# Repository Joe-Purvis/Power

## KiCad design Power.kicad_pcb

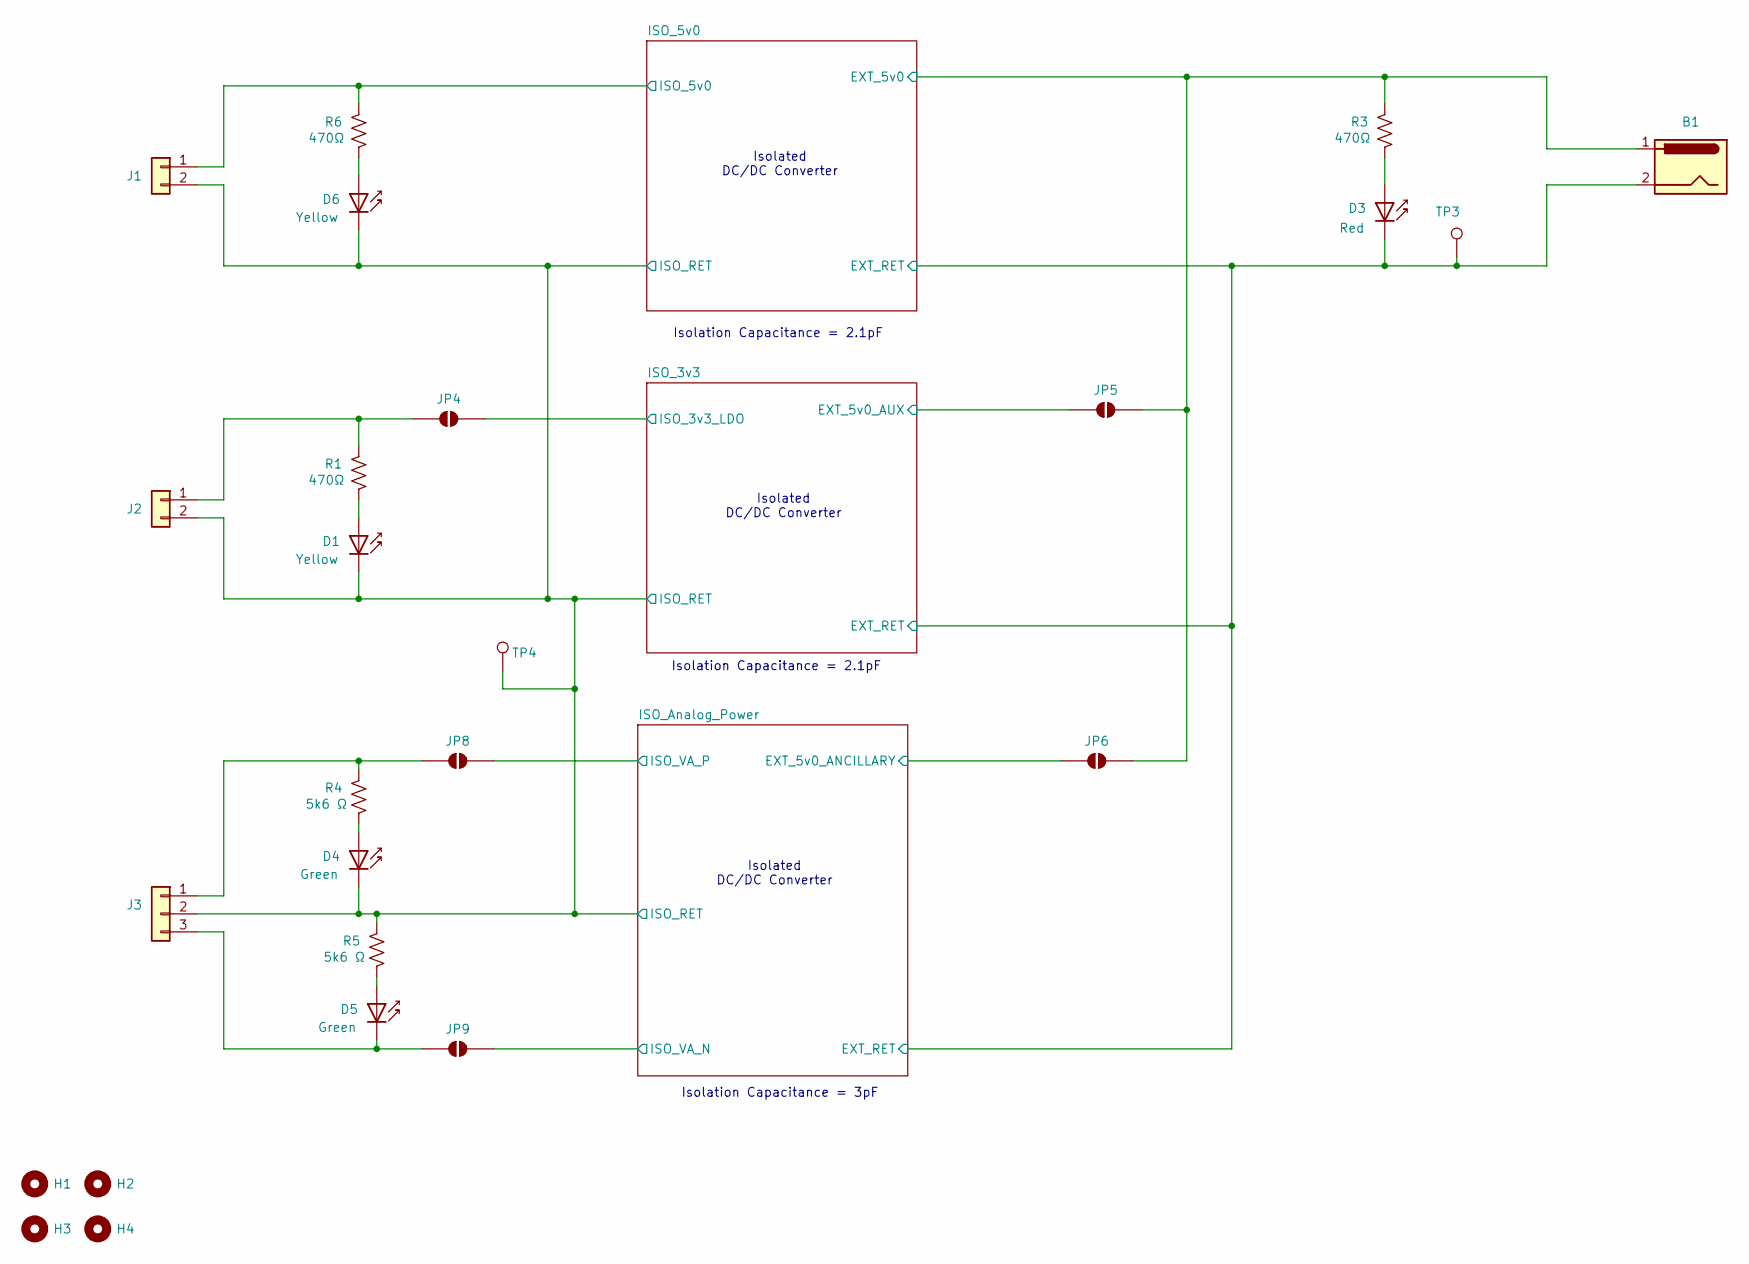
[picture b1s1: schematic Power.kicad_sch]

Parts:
B1: Barrel_Jack; BarrelJack_CUI_PJ-063AH_Horizontal
D1, D6: Yellow; LED_1206_3216Metric; LCSC C2298
D3: Red; LED_1206_3216Metric; LCSC C49018
D4, D5: Green; LED_1206_3216Metric; LCSC C14641
H1, H2, H3, H4: MountingHole; MountingHole_2.2mm_M2
J1, J2: Conn_01x02; PinHeader_1x02_P2.54mm_Vertical
J3: Conn_01x03; PinHeader_1x03_P2.54mm_Vertical
JP4, JP5, JP6, JP8, JP9: SolderJumper_2_Open; SolderJumper-2_P1.3mm_Open_RoundedPad1.0x1.5mm
R1, R3, R6: 470Ω; R_1206_3216Metric_Pad1.30x1.75mm_HandSolder; LCSC C4502
R4, R5: 5k6 Ω; R_1206_3216Metric_Pad1.30x1.75mm_HandSolder; Tolerance 5%; LCSC C2889795
TP3, TP4: TestPoint; TestPoint_Keystone_5000-5004_Miniature

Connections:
/ISO_3v3/EXT_5v0_AUX: JP5.1 (A); also elsewhere on the board
/ISO_3v3/EXT_RET: B1.2, D3.1 (K), TP3.1 (1_1); also elsewhere on the board
/ISO_3v3/ISO_3v3_LDO: JP4.2 (B); also elsewhere on the board
/ISO_5v0/EXT_5v0: B1.1, JP5.2 (B), JP6.2 (B), R3.2; also elsewhere on the board
/ISO_5v0/ISO_5v0: J1.1, R6.2; also elsewhere on the board
/ISO_Analog_Power/EXT_5v0_ANCILLARY: JP6.1 (A); also elsewhere on the board
/ISO_Analog_Power/ISO_RET: D1.1 (K), D4.1 (K), D6.1 (K), J1.2, J2.2, J3.2, R5.2, TP4.1 (1_1); also elsewhere on the board
/ISO_Analog_Power/ISO_VA_N: JP9.2 (B); also elsewhere on the board
/ISO_Analog_Power/ISO_VA_P: JP8.2 (B); also elsewhere on the board
unnamed: D1.2 (A), R1.1
unnamed: D3.2 (A), R3.1
unnamed: D4.2 (A), R4.1
unnamed: D5.2 (A), R5.1
unnamed: D5.1 (K), J3.3, JP9.1 (A)
unnamed: D6.2 (A), R6.1
unnamed: J2.1, JP4.1 (A), R1.2
unnamed: J3.1, JP8.1 (A), R4.2

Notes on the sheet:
Isolated DC/DC Converter
Isolation Capacitance = 2.1pF
Isolation Capacitance = 3pF

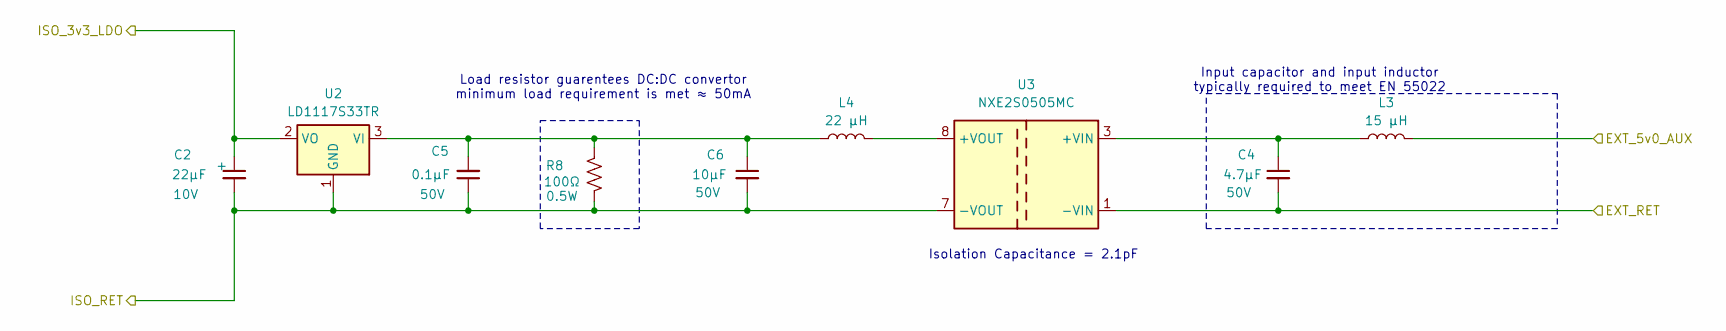
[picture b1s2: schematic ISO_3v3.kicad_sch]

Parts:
C2: 22µF; CP_EIA-3216-18_Kemet-A; Voltage Rating 10V; Tolerance 10%; LCSC C503893
C4: 4.7µF; C_1206_3216Metric; Voltage Rating 50V; LCSC C29823
C5: 0.1µF; C_1206_3216Metric_Pad1.33x1.80mm_HandSolder; Voltage Rating 50V; LCSC C24497
C6: 10µF; C_1206_3216Metric_Pad1.33x1.80mm_HandSolder; Voltage Rating 50V; LCSC C13585
L3: 15 µH; L_Changjiang_FNR4018S; Current Rating 1A; LCSC C167809
L4: 22 µH; L_Sunlord_SWPA5040; Current Rating 1.5A; LCSC C68434
R8: 100Ω; R_1206_3216Metric_Pad1.30x1.75mm_HandSolder; Voltage Rating 7.07V power-limited at 0.5W; series lim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; Tolerance 1%; LCSC C2978216
U2: LD1117S33TR; SOT-223-3_TabPin2; LCSC C86781
U3: NXE2S0505MC; Converter_DCDC_Murata_NXExSxxxxMC_SMD; LCSC C5817088

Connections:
/ISO_3v3/EXT_5v0_AUX: L3.2; also elsewhere on the board
/ISO_3v3/EXT_RET: C4.2, U3.1 (-VIN); also elsewhere on the board
/ISO_3v3/ISO_3v3_LDO: C2.1, U2.2 (VO); also elsewhere on the board
/ISO_Analog_Power/ISO_RET: C2.2, C5.1, C6.2, R8.1, U2.1 (GND), U3.7 (-VOUT); also elsewhere on the board
unnamed: C5.2, C6.1, L4.1, R8.2, U2.3 (VI)
unnamed: C4.1, L3.1, U3.3 (+VIN)
unnamed: L4.2, U3.8 (+VOUT)

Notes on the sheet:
Load resistor guarentees DC:DC convertor minimum load requirement is met ≈ 50mA
Input capacitor and input inductor typically required to meet EN 55022
Isolation Capacitance = 2.1pF

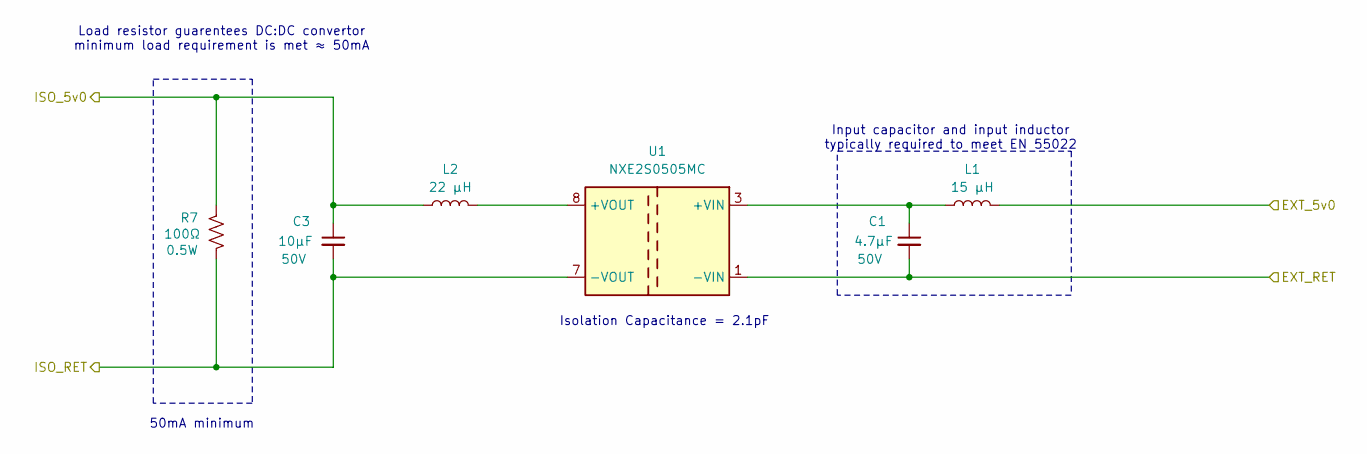
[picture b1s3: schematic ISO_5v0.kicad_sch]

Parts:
C1: 4.7µF; C_1206_3216Metric; Voltage Rating 50V; LCSC C29823
C3: 10µF; C_1206_3216Metric_Pad1.33x1.80mm_HandSolder; Voltage Rating 50V; LCSC C13585
L1: 15 µH; L_Changjiang_FNR4018S; Current Rating 1A; LCSC C167809
L2: 22 µH; L_Sunlord_SWPA5040; Current Rating 1.5A; LCSC C68434
R7: 100Ω; R_1206_3216Metric_Pad1.30x1.75mm_HandSolder; Voltage Rating 7.07V power-limited at 0.5W; series lim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; Tolerance 1%; LCSC C2978216
U1: NXE2S0505MC; Converter_DCDC_Murata_NXExSxxxxMC_SMD; LCSC C5817088

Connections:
/ISO_3v3/EXT_RET: C1.2, U1.1 (-VIN); also elsewhere on the board
/ISO_5v0/EXT_5v0: L1.2; also elsewhere on the board
/ISO_5v0/ISO_5v0: C3.1, L2.1, R7.2; also elsewhere on the board
/ISO_Analog_Power/ISO_RET: C3.2, R7.1, U1.7 (-VOUT); also elsewhere on the board
unnamed: C1.1, L1.1, U1.3 (+VIN)
unnamed: L2.2, U1.8 (+VOUT)

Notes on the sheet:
Load resistor guarentees DC:DC convertor minimum load requirement is met ≈ 50mA
Isolation Capacitance = 2.1pF
Input capacitor and input inductor typically required to meet EN 55022
50mA minimum

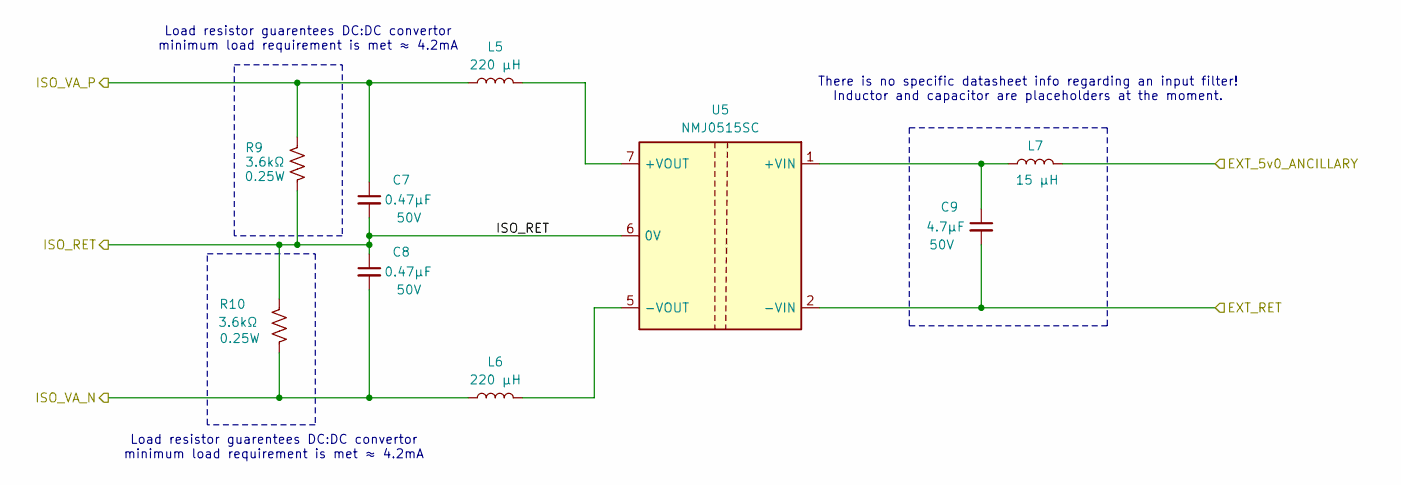
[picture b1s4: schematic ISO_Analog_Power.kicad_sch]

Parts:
C7, C8: 0.47µF; C_1206_3216Metric_Pad1.33x1.80mm_HandSolder; Voltage Rating 50V; LCSC C277483
C9: 4.7µF; C_1206_3216Metric; Voltage Rating 50V; LCSC C29823
L5, L6: 220 µH; L_Sunlord_SWPA4030; Current Rating 0.35A; LCSC C62495
L7: 15 µH; L_Changjiang_FNR4018S; Current Rating 1A; LCSC C167809
R9, R10: 3.6kΩ; R_1206_3216Metric_Pad1.30x1.75mm_HandSolder; Voltage Rating 30V power-limited at 0.25W; series limi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; Tolerance 1%; LCSC C137291
U5: NMJ0515SC

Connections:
/ISO_3v3/EXT_RET: C9.2, U5.2 (-VIN); also elsewhere on the board
/ISO_Analog_Power/EXT_5v0_ANCILLARY: L7.2; also elsewhere on the board
/ISO_Analog_Power/ISO_RET: C7.2, C8.1, R9.1, R10.2, U5.6 (0V); also elsewhere on the board
/ISO_Analog_Power/ISO_VA_N: C8.2, L6.1, R10.1; also elsewhere on the board
/ISO_Analog_Power/ISO_VA_P: C7.1, L5.1, R9.2; also elsewhere on the board
unnamed: C9.1, L7.1, U5.1 (+VIN)
unnamed: L5.2, U5.7 (+VOUT)
unnamed: L6.2, U5.5 (-VOUT)

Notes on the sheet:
Load resistor guarentees DC:DC convertor minimum load requirement is met ≈ 4.2mA
There is no specific datasheet info regarding an input filter! Inductor and capacitor are placeholders at the moment.

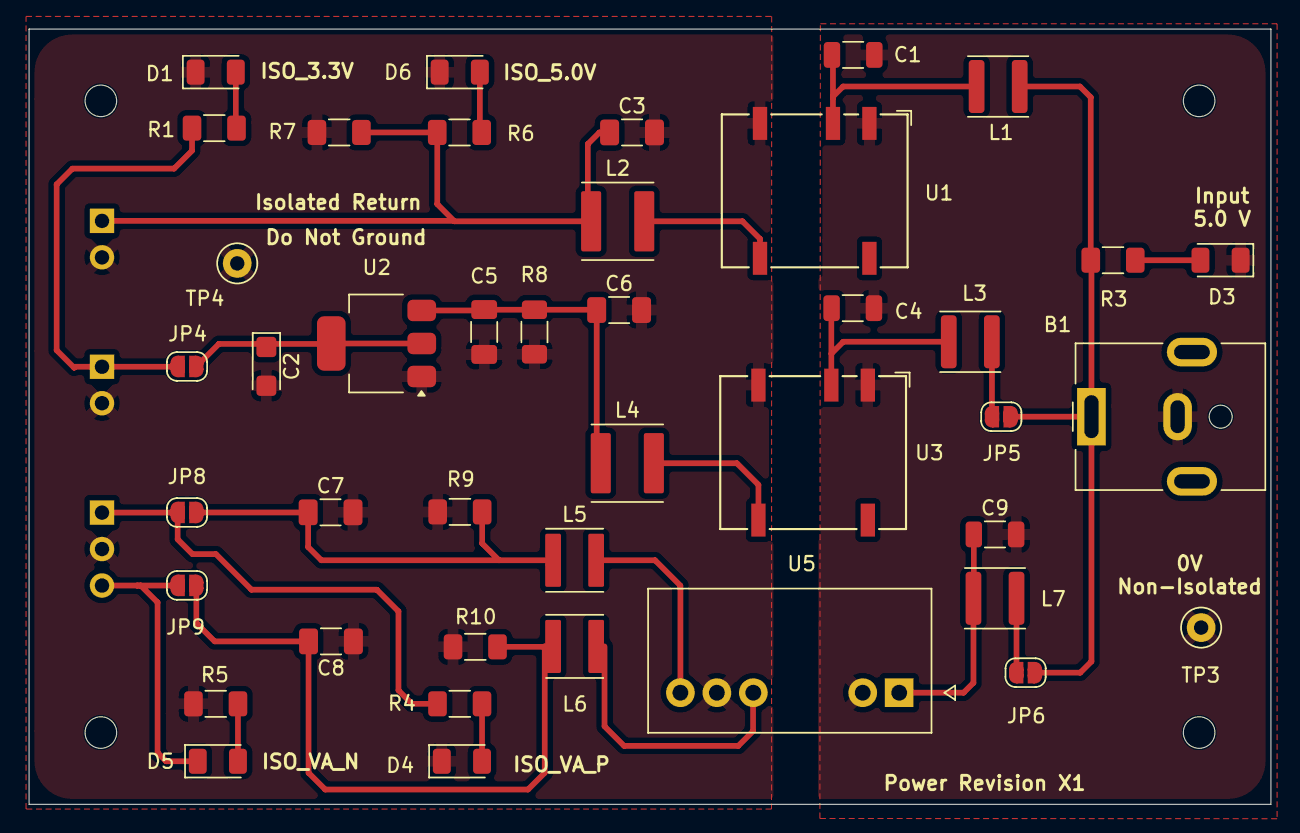
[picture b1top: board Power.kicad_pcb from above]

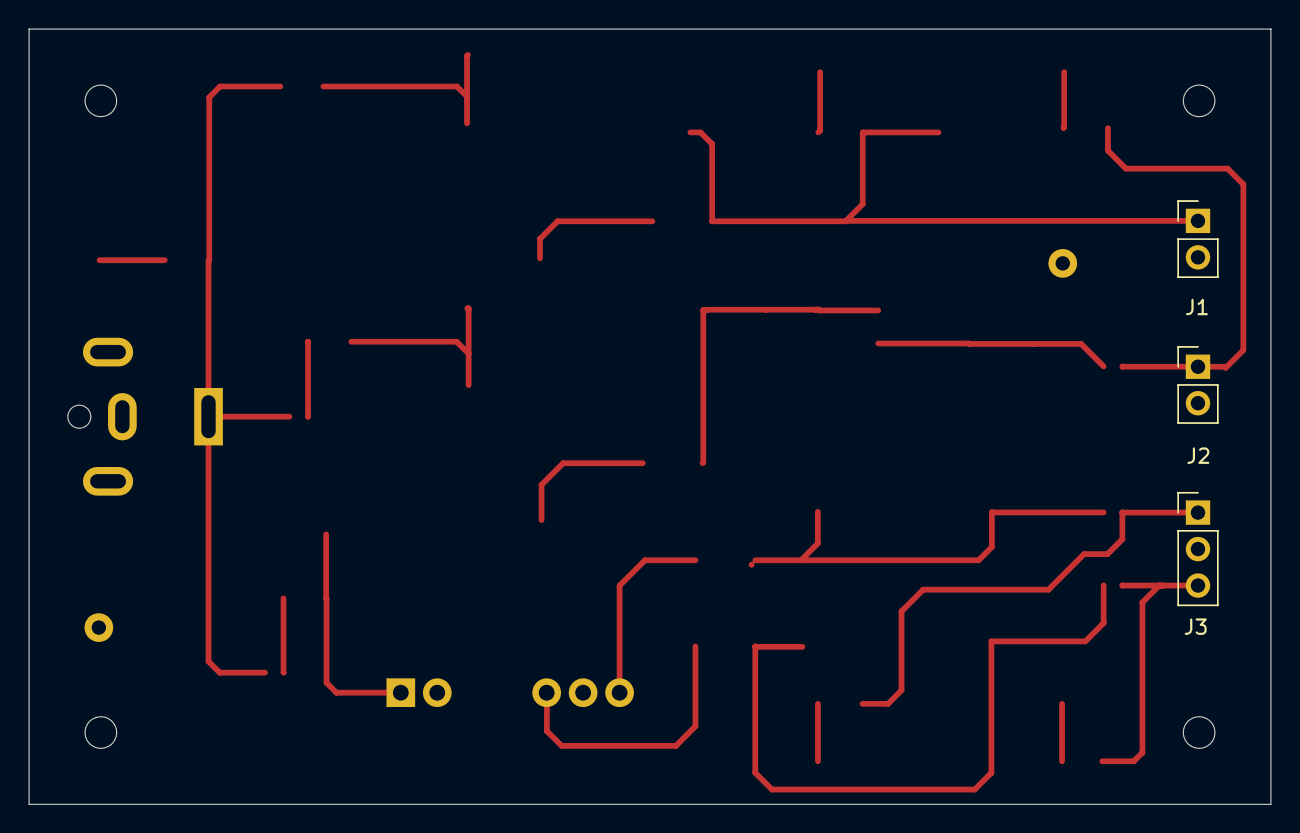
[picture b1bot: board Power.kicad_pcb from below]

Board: 2 copper layers, 86.5 x 54.0 mm, 50 parts (3 on the bottom side), 25 nets.

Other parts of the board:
QR1: LogicPower_Repo_QR; LogicPower_QR_Code
